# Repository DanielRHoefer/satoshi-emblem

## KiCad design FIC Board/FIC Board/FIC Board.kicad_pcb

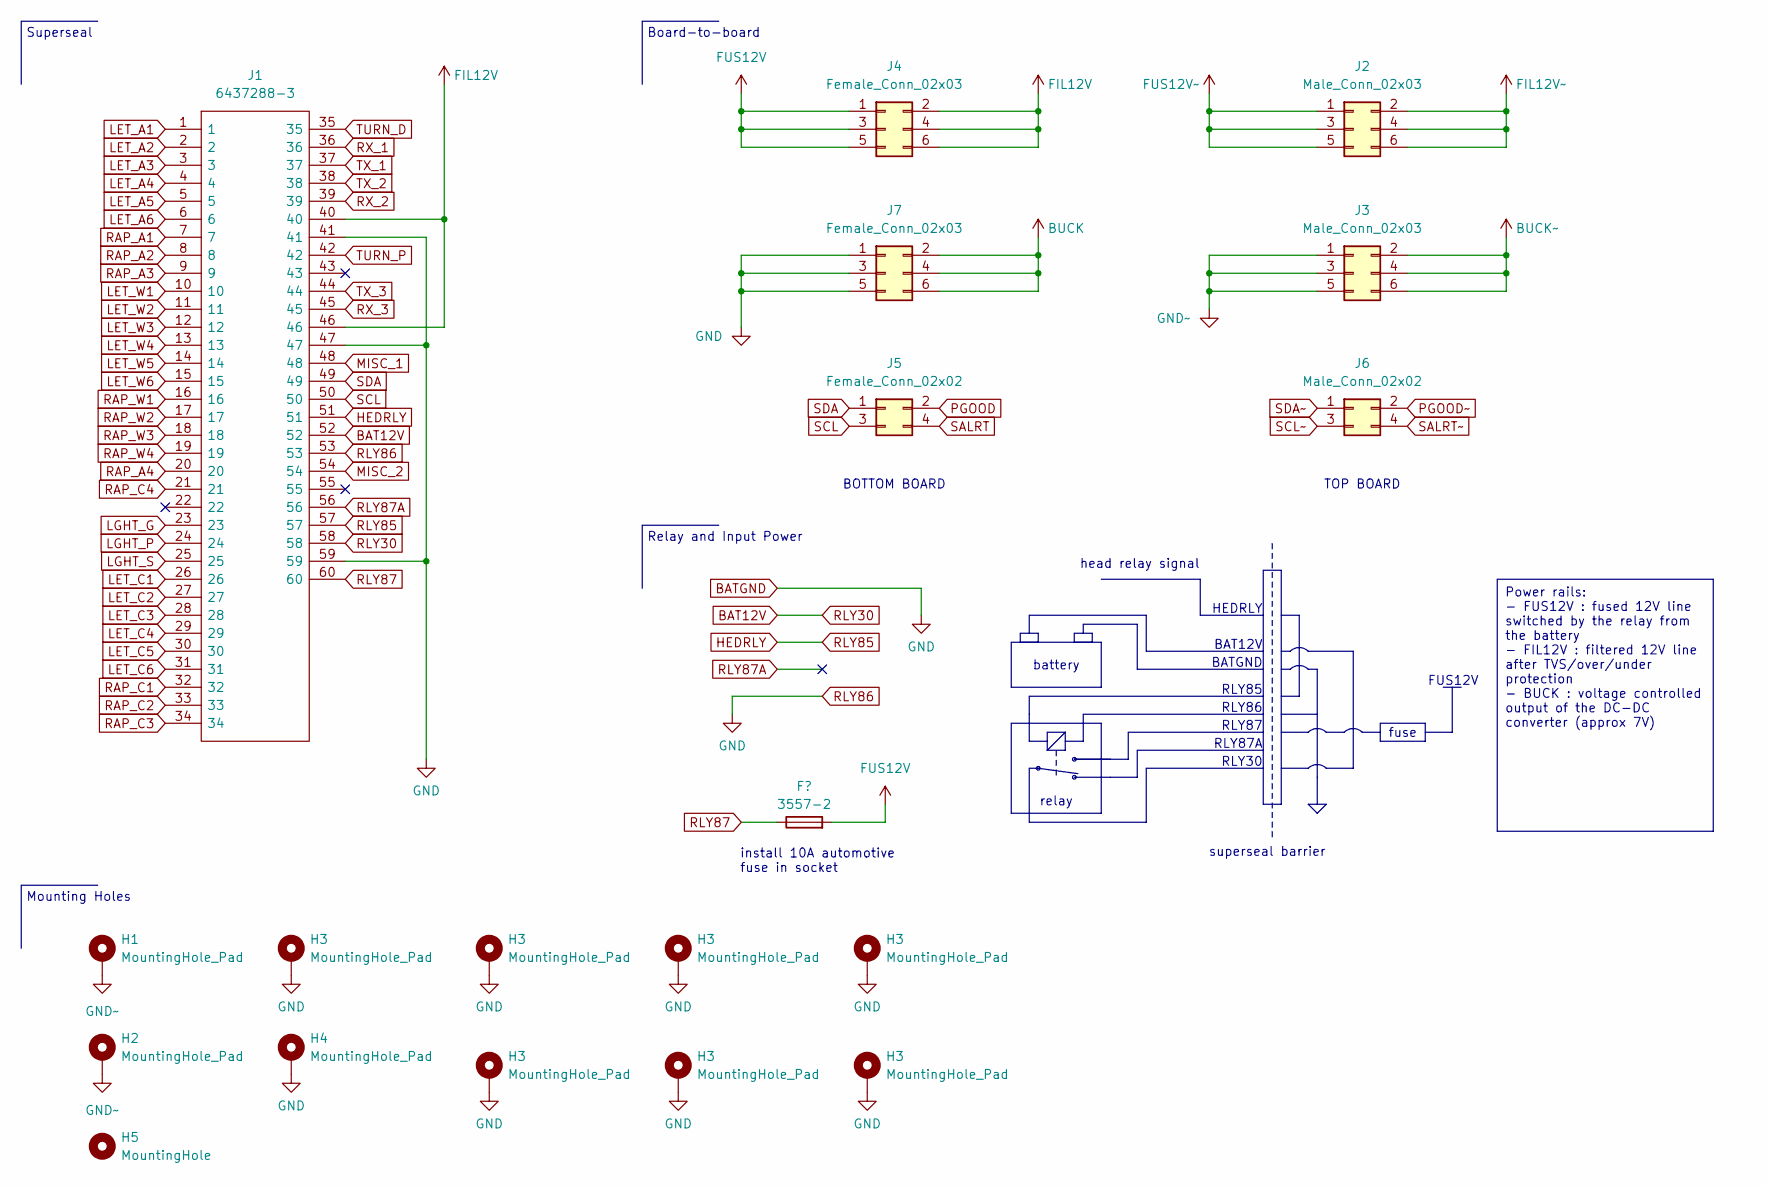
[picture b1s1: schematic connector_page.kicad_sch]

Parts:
F1: 3557-2; Univ_AUTO_Fuse; MPN 3557-2
H1, H2, H3, H4: MountingHole_Pad; MountingHole_2.7mm_M2.5_Pad_TopBottom
H5: MountingHole; MountingHole_2.7mm_M2.5
J1: 6437288-3; 64372885; MPN 6437288-3; Mouser Part Number 571-6437288-5
J2, J3: Conn_02x03_Odd_Even; Male_3x2_Conn
J4: Female_3x2_Conn
J5: Conn_02x02_Odd_Even; Female_2x2_Conn
J6: Conn_02x02_Odd_Even; Male_2x2_Conn
J7: Conn_02x03_Odd_Even; Female_3x2_Conn

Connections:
BAT12V: J1.52, J1.58
BUCK~: J3.2, J3.4, J3.6; also elsewhere on the board
FIL12V: J1.40, J1.46, J4.2, J4.4, J4.6
FIL12V~: J2.2, J2.4, J2.6; also elsewhere on the board
FUS12V: F1.2, J4.1, J4.3, J4.5
FUS12V~: J2.1, J2.3, J2.5; also elsewhere on the board
HEDRLY: J1.51, J1.57
LET_A1: J1.1; also elsewhere on the board
LET_A2: J1.2; also elsewhere on the board
LET_A3: J1.3; also elsewhere on the board
LET_A4: J1.4; also elsewhere on the board
LET_A5: J1.5; also elsewhere on the board
LET_A6: J1.6; also elsewhere on the board
LET_W1: J1.10; also elsewhere on the board
LET_W2: J1.11; also elsewhere on the board
LET_W3: J1.12; also elsewhere on the board
LET_W4: J1.13; also elsewhere on the board
LET_W5: J1.14; also elsewhere on the board
LET_W6: J1.15; also elsewhere on the board
LGHT_S: J1.25; also elsewhere on the board
MISC_1: J1.48; also elsewhere on the board
MISC_2: J1.54; also elsewhere on the board
PGOOD: J5.2; also elsewhere on the board
PGOOD~: J6.2; also elsewhere on the board
RAP_A1: J1.7; also elsewhere on the board
RAP_A2: J1.8; also elsewhere on the board
RAP_A3: J1.9; also elsewhere on the board
RAP_A4: J1.20; also elsewhere on the board
RAP_W1: J1.16; also elsewhere on the board
RAP_W2: J1.17; also elsewhere on the board
RAP_W3: J1.18; also elsewhere on the board
RAP_W4: J1.19; also elsewhere on the board
RLY87: F1.1, J1.60
RLY87A: J1.56
RX_1: J1.36; also elsewhere on the board
RX_2: J1.39; also elsewhere on the board
RX_3: J1.45; also elsewhere on the board
SALRT: J5.4; also elsewhere on the board
SALRT~: J6.4; also elsewhere on the board
SCL~: J6.3; also elsewhere on the board
SDA~: J6.1; also elsewhere on the board
TURN_D: J1.35; also elsewhere on the board
TURN_P: J1.42; also elsewhere on the board
TX_1: J1.37; also elsewhere on the board
TX_2: J1.38; also elsewhere on the board
TX_3: J1.44; also elsewhere on the board

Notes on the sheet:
fuse
relay
battery
install 10A automotive fuse in socket
BOTTOM BOARD
TOP BOARD
Power rails: - FUS12V : fused 12V line switched by the relay from the battery - FIL12V : filtered 12V line after TVS/over/under protection - BUCK : voltage controlled output of the DC-DC converter (approx 7V)
Board-to-board
Mounting Holes
BATGND
RLY87
BAT12V
RLY86
head relay signal
superseal barrier
HEDRLY
FUS12V
RLY30
RLY87A
Superseal
Relay and Input Power
RLY85

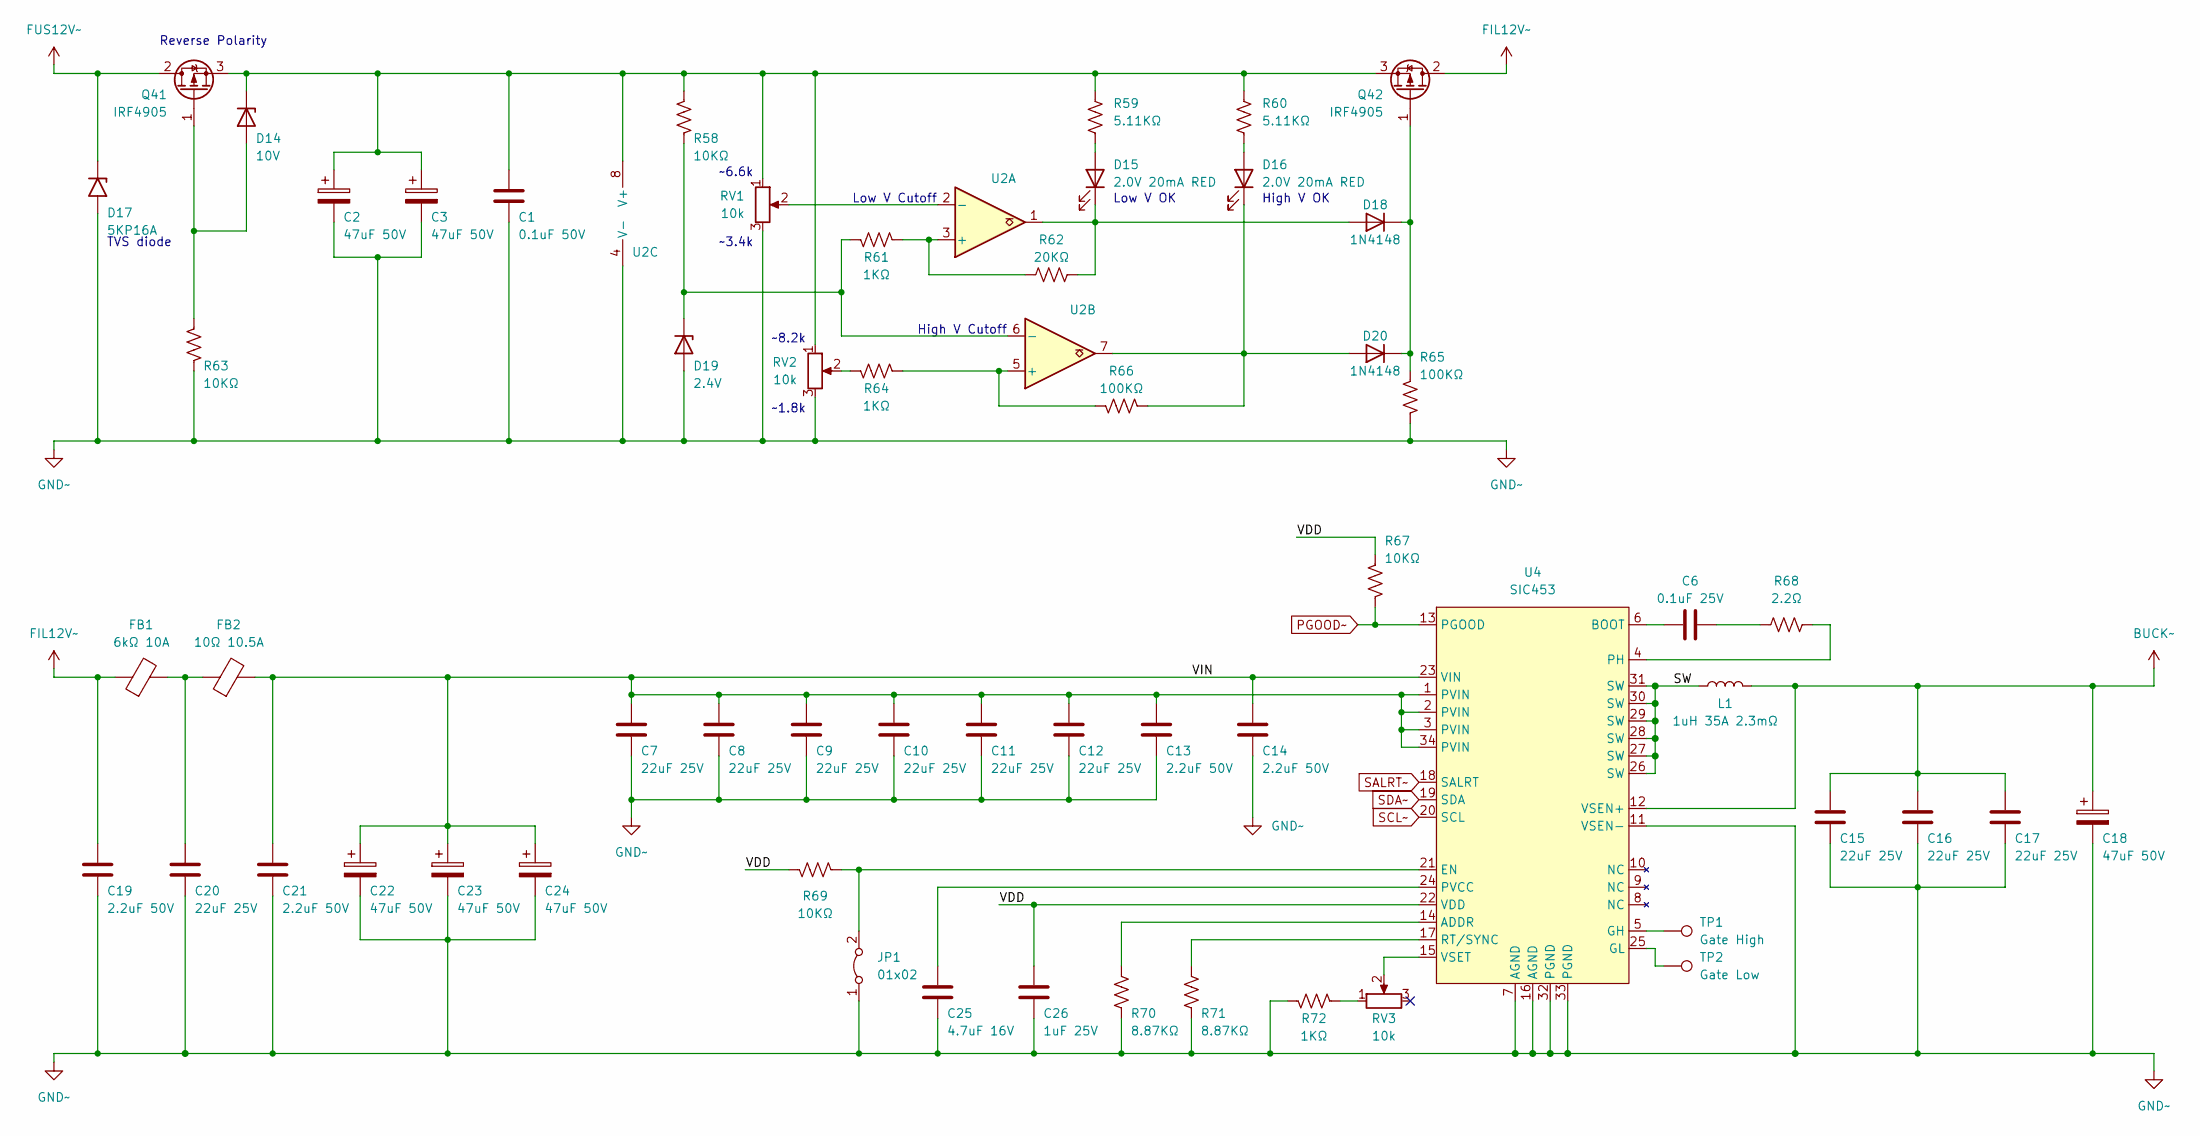
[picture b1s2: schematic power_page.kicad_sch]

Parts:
C1: 0.1u 50V; C_Disc_D4.7mm_W2.5mm_P5.00mm; MPN C322C104K5R5TA7317
C2, C3, C18, C22, C23, C24: 47uF 50V; CP_Elec_6.3x5.9; MPN 865080645012
C6: 0.1uF; C_0603_1608Metric; MPN KGM15BR71E104KM
C7, C8, C9, C10, C11, C12, C15, C16, C17, C20: 22uF 25V; C_1210_3225Metric; MPN CL32B226KAJNNNE
C13, C14, C19, C21: 2.2uF 50V; C_0603_1608Metric; MPN GRM188R61H225ME11D
C25: 4.7u; C_0603_1608Metric; MPN GRM188Z71C475KE21J
C26: 1uF 25V; C_0603_1608Metric; MPN CL10B105KA8NNNC
D14: 10V Zener SOD-80; D_MiniMELF; MPN BZT55B10-GS08
D15, D16: LED_0603_1608Metric; MPN LTST-C191KRKT
D17: 5KP16A; D_P600_R-6_P20.00mm_Horizontal; MPN 5KP16A
D18, D20: 1N4148W-13-F; D_SOD-123; MPN 1N4148W-13-F
D19: 2.4V Zener SOD-80; D_MiniMELF; MPN TZM5221B-GS08
FB1: 74279221100; L_1206_3216Metric_Pad1.22x1.90mm_HandSolder; MPN 742792903
FB2: 74279221100; Wurth 742792903 L_12x12mm_H8mm; MPN 74279221100
JP1: Jumper_2_Bridged; MaleHeader_1x2_conn
L1: SRP1265C-1R0M; INDPM135126X650N; MPN SRP1265C-1R0M
Q41, Q42: IRF4905; TO-263-2; MPN IRF4905STRLPBF
R58, R63, R67, R69: 10KΩ 0603; R_0603_1608Metric; MPN RNCP0603FTD10K0
R59, R60: 5.11KΩ; R_0603_1608Metric; MPN RNCP0603FTD5K11
R61, R64, R72: 1KΩ 0603; R_0603_1608Metric; MPN RNCP0603FTD1K00
R62: 20K; R_0603_1608Metric; MPN RNCP0603FTD20K0
R65, R66: 100KΩ 0603; R_0603_1608Metric; MPN ERJ-H3EF1003V
R68: 2.2Ω; R_0603_1608Metric; MPN RC0603FR-072R2L
R70, R71: 8.87KΩ; R_0603_1608Metric; MPN CRCW06038R87FKEA
RV1, RV2, RV3: 10k; Potentiometer_Bourns_3296X_Horizontal; MPN 3296X-1-103LF
TP1, TP2: TestPoint; TestPoint_Pad_1.0x1.0mm
U2: LM393DR; SOIC-8_3.9x4.9mm_P1.27mm; MPN LM393DR
U4: SIC453ED-T1-GE3; SiC45X; MPN SIC453ED-T1-GE3

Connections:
/POWER/SW: L1.1, U4.26 (SW), U4.27 (SW), U4.28 (SW), U4.29 (SW), U4.30 (SW), U4.31 (SW)
/POWER/VDD: C26.1, R67.1, R69.1, U4.22 (VDD)
/POWER/VIN: C7.1, C8.1, C9.1, C10.1, C11.1, C12.1, C13.1, C14.1, C21.1, C22.1, C23.1, C24.1, FB2.2, U4.1 (PVIN), U4.2 (PVIN), U4.3 (PVIN), U4.23 (VIN), U4.34 (PVIN)
BUCK~: C15.1, C16.1, C17.1, C18.1, L1.2, U4.12 (VSEN+); also elsewhere on the board
FIL12V~: C19.1, FB1.1, Q42.2 (D); also elsewhere on the board
FUS12V~: D17.1 (A1), Q41.2 (D); also elsewhere on the board
unnamed: C20.1, FB1.2, FB2.1
unnamed: D14.2 (A), Q41.1 (G), R63.1
unnamed: D15.2 (A), R59.2
unnamed: D15.1 (K), D18.2 (A), R62.2, U2.1
unnamed: D16.2 (A), R60.2
unnamed: D16.1 (K), D20.2 (A), R66.2, U2.7
unnamed: D18.1 (K), D20.1 (K), Q42.1 (G), R65.1
unnamed: JP1.2 (B), R69.2, U4.21 (EN)
unnamed: R64.1, RV2.2
unnamed: R72.2, RV3.1
unnamed: R61.2, R62.1, U2.3 (+)
unnamed: RV1.2, U2.2 (-)
unnamed: R64.2, R66.1, U2.5 (+)
unnamed: R70.1, U4.14 (ADDR)
unnamed: TP1.1, U4.5 (GH)
unnamed: TP2.1, U4.25 (GL)
unnamed: R68.2, U4.4 (PH)
unnamed: C25.1, U4.24 (PVCC)
unnamed: R71.1, U4.17 (RT/SYNC)
unnamed: RV3.2, U4.15 (VSET)
PGOOD~: R67.2, U4.13 (PGOOD); also elsewhere on the board
SALRT~: U4.18 (SALRT); also elsewhere on the board
SCL~: U4.20 (SCL); also elsewhere on the board
SDA~: U4.19 (SDA); also elsewhere on the board

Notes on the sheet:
~8.2k
~3.4k
Reverse Polarity
High V Cutoff
~6.6k
Low V OK
TVS diode
Low V Cutoff
~1.8k
High V OK

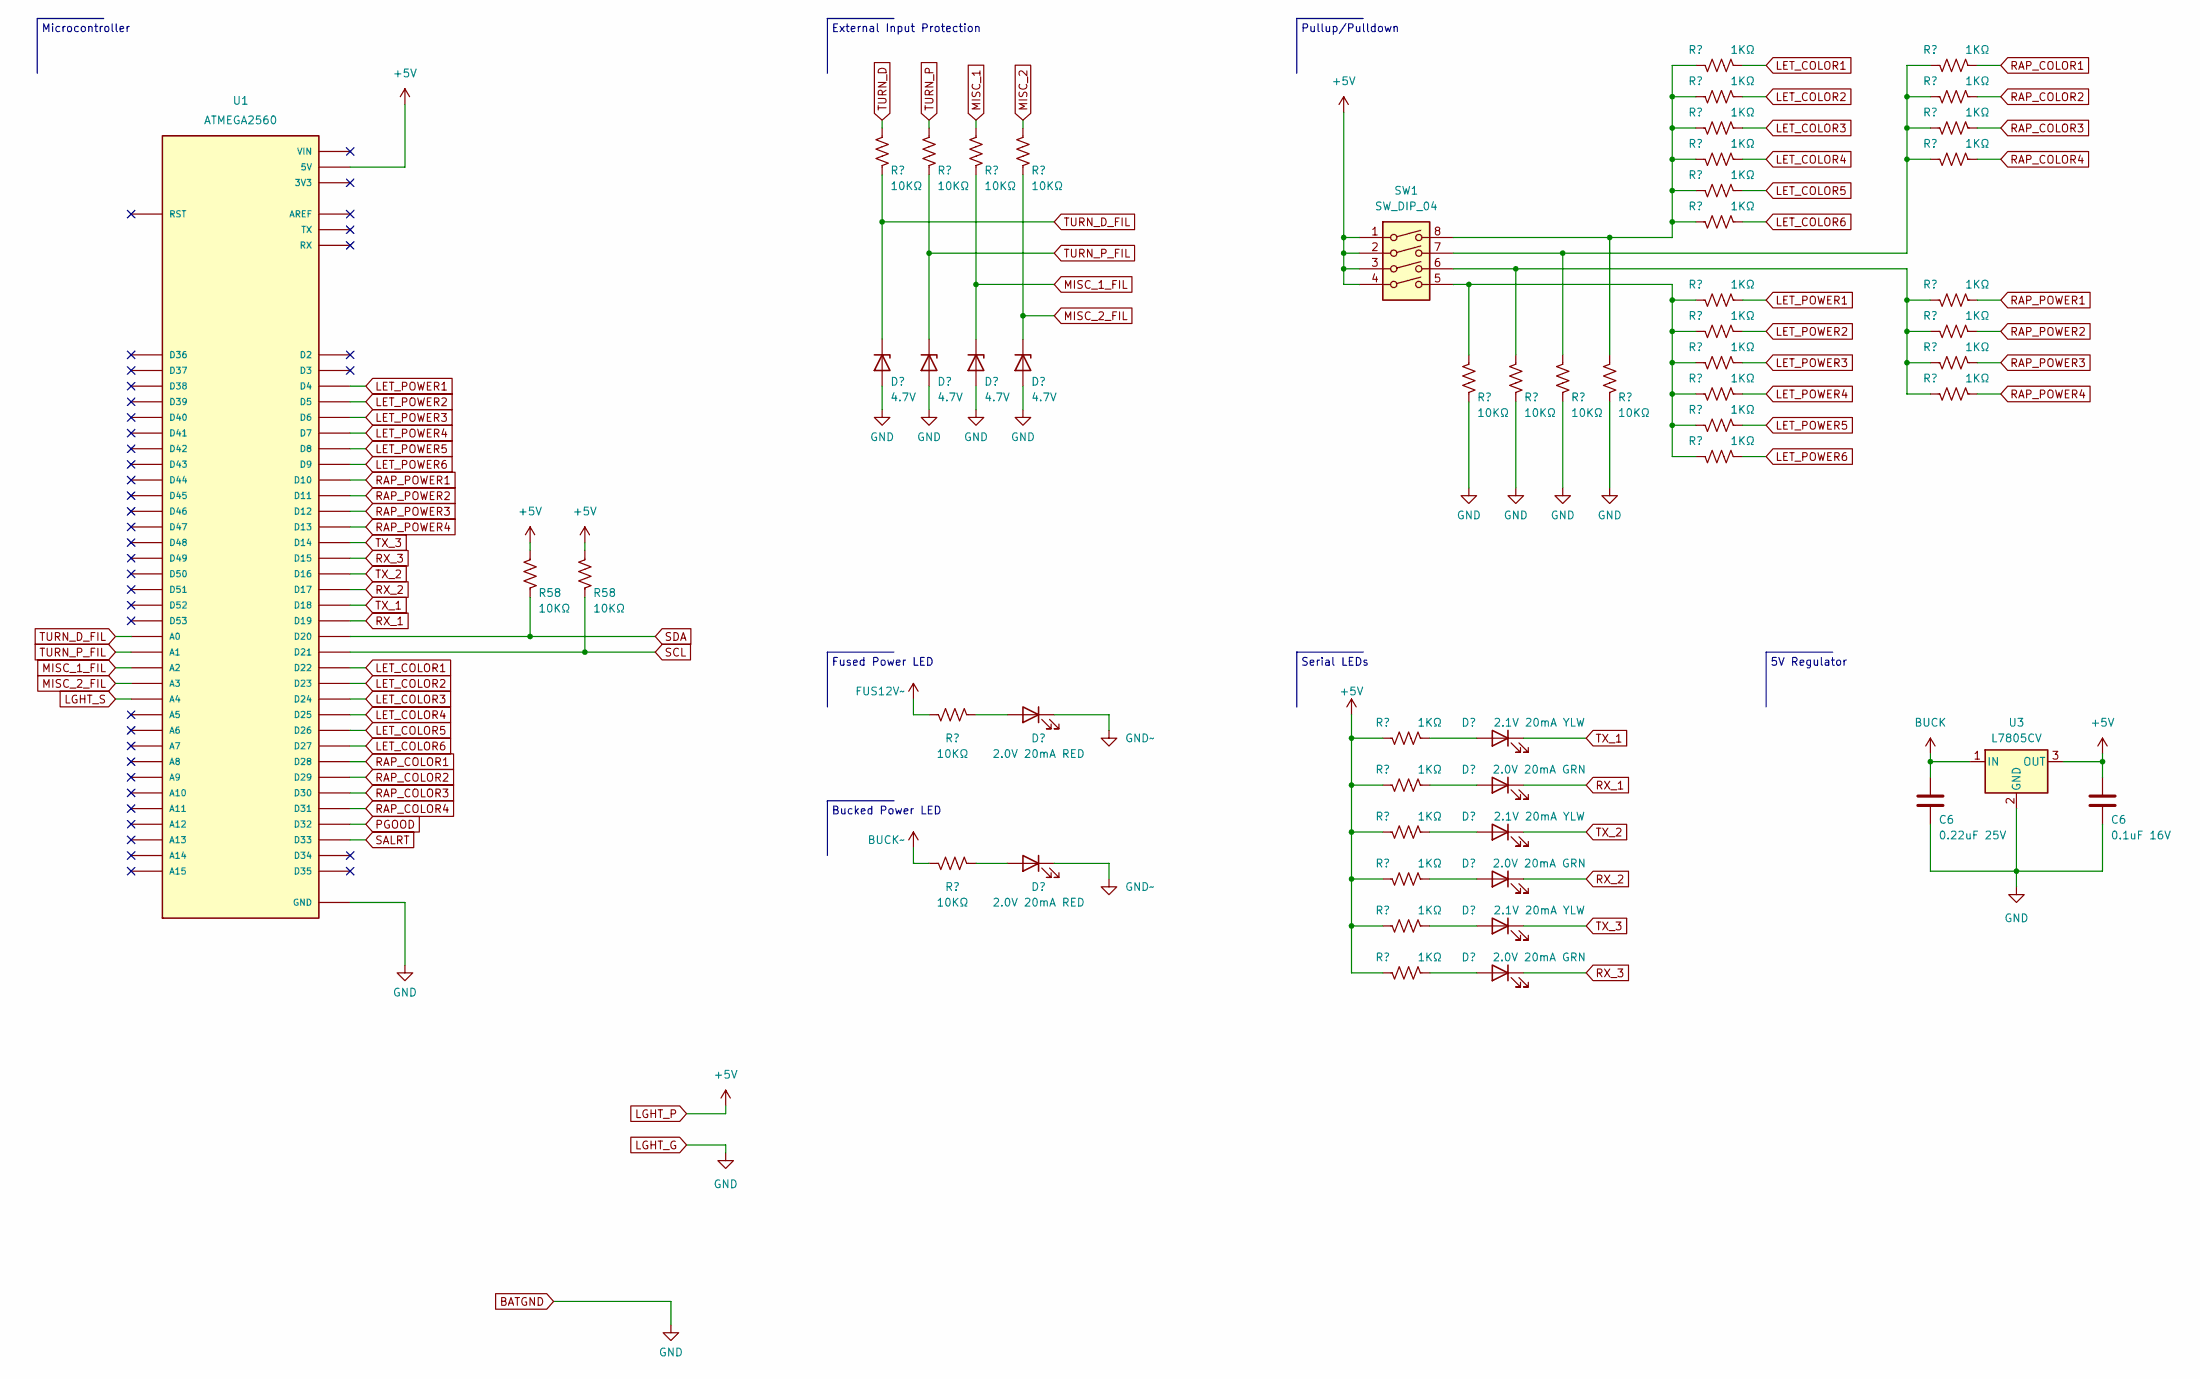
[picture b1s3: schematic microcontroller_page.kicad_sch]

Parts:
C6: KGM15BR51E224KT; C_0603_1608Metric; MPN KGM15BR51E224KT
D1: Diode_SMD:D_MiniMELF; D_MiniMELF; MPN BZT55C4V7-GS08
D2, D3, D4: 4.7V Zener SOD-80; D_MiniMELF; MPN BZT55C4V7-GS08
D6, D8, D11: 2.1V 20mA YLW 0603; LED_0603_1608Metric; MPN LTST-C191KSKT
D7, D10, D12: 2.0V 20mA GRN 0603; LED_0603_1608Metric; MPN LTST-C191KGKT
D9, D13: 2.0V 20mA RED 0603; LED_0603_1608Metric; MPN LTST-C191KRKT
R1, R2, R3, R4, R5, R6, R11, R12, R13, R14, R15, R16, R17, R18, R19, R20, R25, R26, R27, R28, R30, R31, R32, R34, R35, R36: 1KΩ 0603; R_0603_1608Metric; MPN RNCP0603FTD1K00
R7, R8, R9, R10, R21, R22, R23, R24, R33, R37, R58: 10KΩ 0603; R_0603_1608Metric; MPN RNCP0603FTD10K0
SW1: SW_DIP_04; SW_DIP_SPSTx04_Slide_9.78x12.34mm_W7.62mm_P2.54mm; MPN DS01C-254-L-04BE
U1: MEGA_PRO_EMBED_CH340G_/_ATMEGA2560; MODULE_MEGA_PRO_EMBED_CH340G___ATMEGA2560; PARTREV 12/May/2017
U3: L7805CV; TO-220-3_Horizontal_TabDown; MPN L7805CV

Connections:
BUCK~: R37.1; also elsewhere on the board
FUS12V~: R33.1; also elsewhere on the board
LET_COLOR1: R1.2, U1.D22; also elsewhere on the board
LET_COLOR2: R3.2, U1.D23; also elsewhere on the board
LET_COLOR3: R5.2, U1.D24; also elsewhere on the board
LET_COLOR4: R11.2, U1.D25; also elsewhere on the board
LET_COLOR5: R13.2, U1.D26; also elsewhere on the board
LET_COLOR6: R14.2, U1.D27; also elsewhere on the board
LET_POWER1: R15.2, U1.D4; also elsewhere on the board
LET_POWER2: R17.2, U1.D5; also elsewhere on the board
LET_POWER3: R19.2, U1.D6; also elsewhere on the board
LET_POWER4: R25.2, U1.D7; also elsewhere on the board
LET_POWER5: R27.2, U1.D8; also elsewhere on the board
LET_POWER6: R28.2, U1.D9; also elsewhere on the board
LGHT_S: U1.A4; also elsewhere on the board
MISC_1: R9.1; also elsewhere on the board
MISC_1_FIL: D3.1 (K), R9.2, U1.A2
MISC_2: R10.1; also elsewhere on the board
MISC_2_FIL: D4.1 (K), R10.2, U1.A3
unnamed: D6.2 (A), R30.2
unnamed: D7.2 (A), R31.2
unnamed: D8.2 (A), R32.2
unnamed: D9.2 (A), R33.2
unnamed: D10.2 (A), R34.2
unnamed: D11.2 (A), R35.2
unnamed: D12.2 (A), R36.2
unnamed: D13.2 (A), R37.2
unnamed: R1.1, R3.1, R5.1, R11.1, R13.1, R14.1, R24.1, SW1.8
unnamed: R2.1, R4.1, R6.1, R12.1, R23.1, SW1.7
unnamed: R15.1, R17.1, R19.1, R21.1, R25.1, R27.1, R28.1, SW1.5
unnamed: R16.1, R18.1, R20.1, R22.1, R26.1, SW1.6
PGOOD: U1.D32; also elsewhere on the board
RAP_COLOR1: R2.2, U1.D28; also elsewhere on the board
RAP_COLOR2: R4.2, U1.D29; also elsewhere on the board
RAP_COLOR3: R6.2, U1.D30; also elsewhere on the board
RAP_POWER1: R16.2, U1.D10; also elsewhere on the board
RAP_POWER2: R18.2, U1.D11; also elsewhere on the board
RAP_POWER3: R20.2, U1.D12; also elsewhere on the board
RAP_POWER4: R26.2, U1.D13; also elsewhere on the board
RX_1: D7.1 (K), U1.D19; also elsewhere on the board
RX_2: D10.1 (K), U1.D17; also elsewhere on the board
RX_3: D12.1 (K), U1.D15; also elsewhere on the board
SALRT: U1.D33; also elsewhere on the board
TURN_D: R7.1; also elsewhere on the board
TURN_D_FIL: D1.1 (K), R7.2, U1.A0
TURN_P: R8.1; also elsewhere on the board
TURN_P_FIL: D2.1 (K), R8.2, U1.A1
TX_1: D6.1 (K), U1.D18; also elsewhere on the board
TX_2: D8.1 (K), U1.D16; also elsewhere on the board
TX_3: D11.1 (K), U1.D14; also elsewhere on the board

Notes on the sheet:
Fused Power LED
Bucked Power LED
Pullup/Pulldown
Serial LEDs
5V Regulator
Microcontroller
External Input Protection

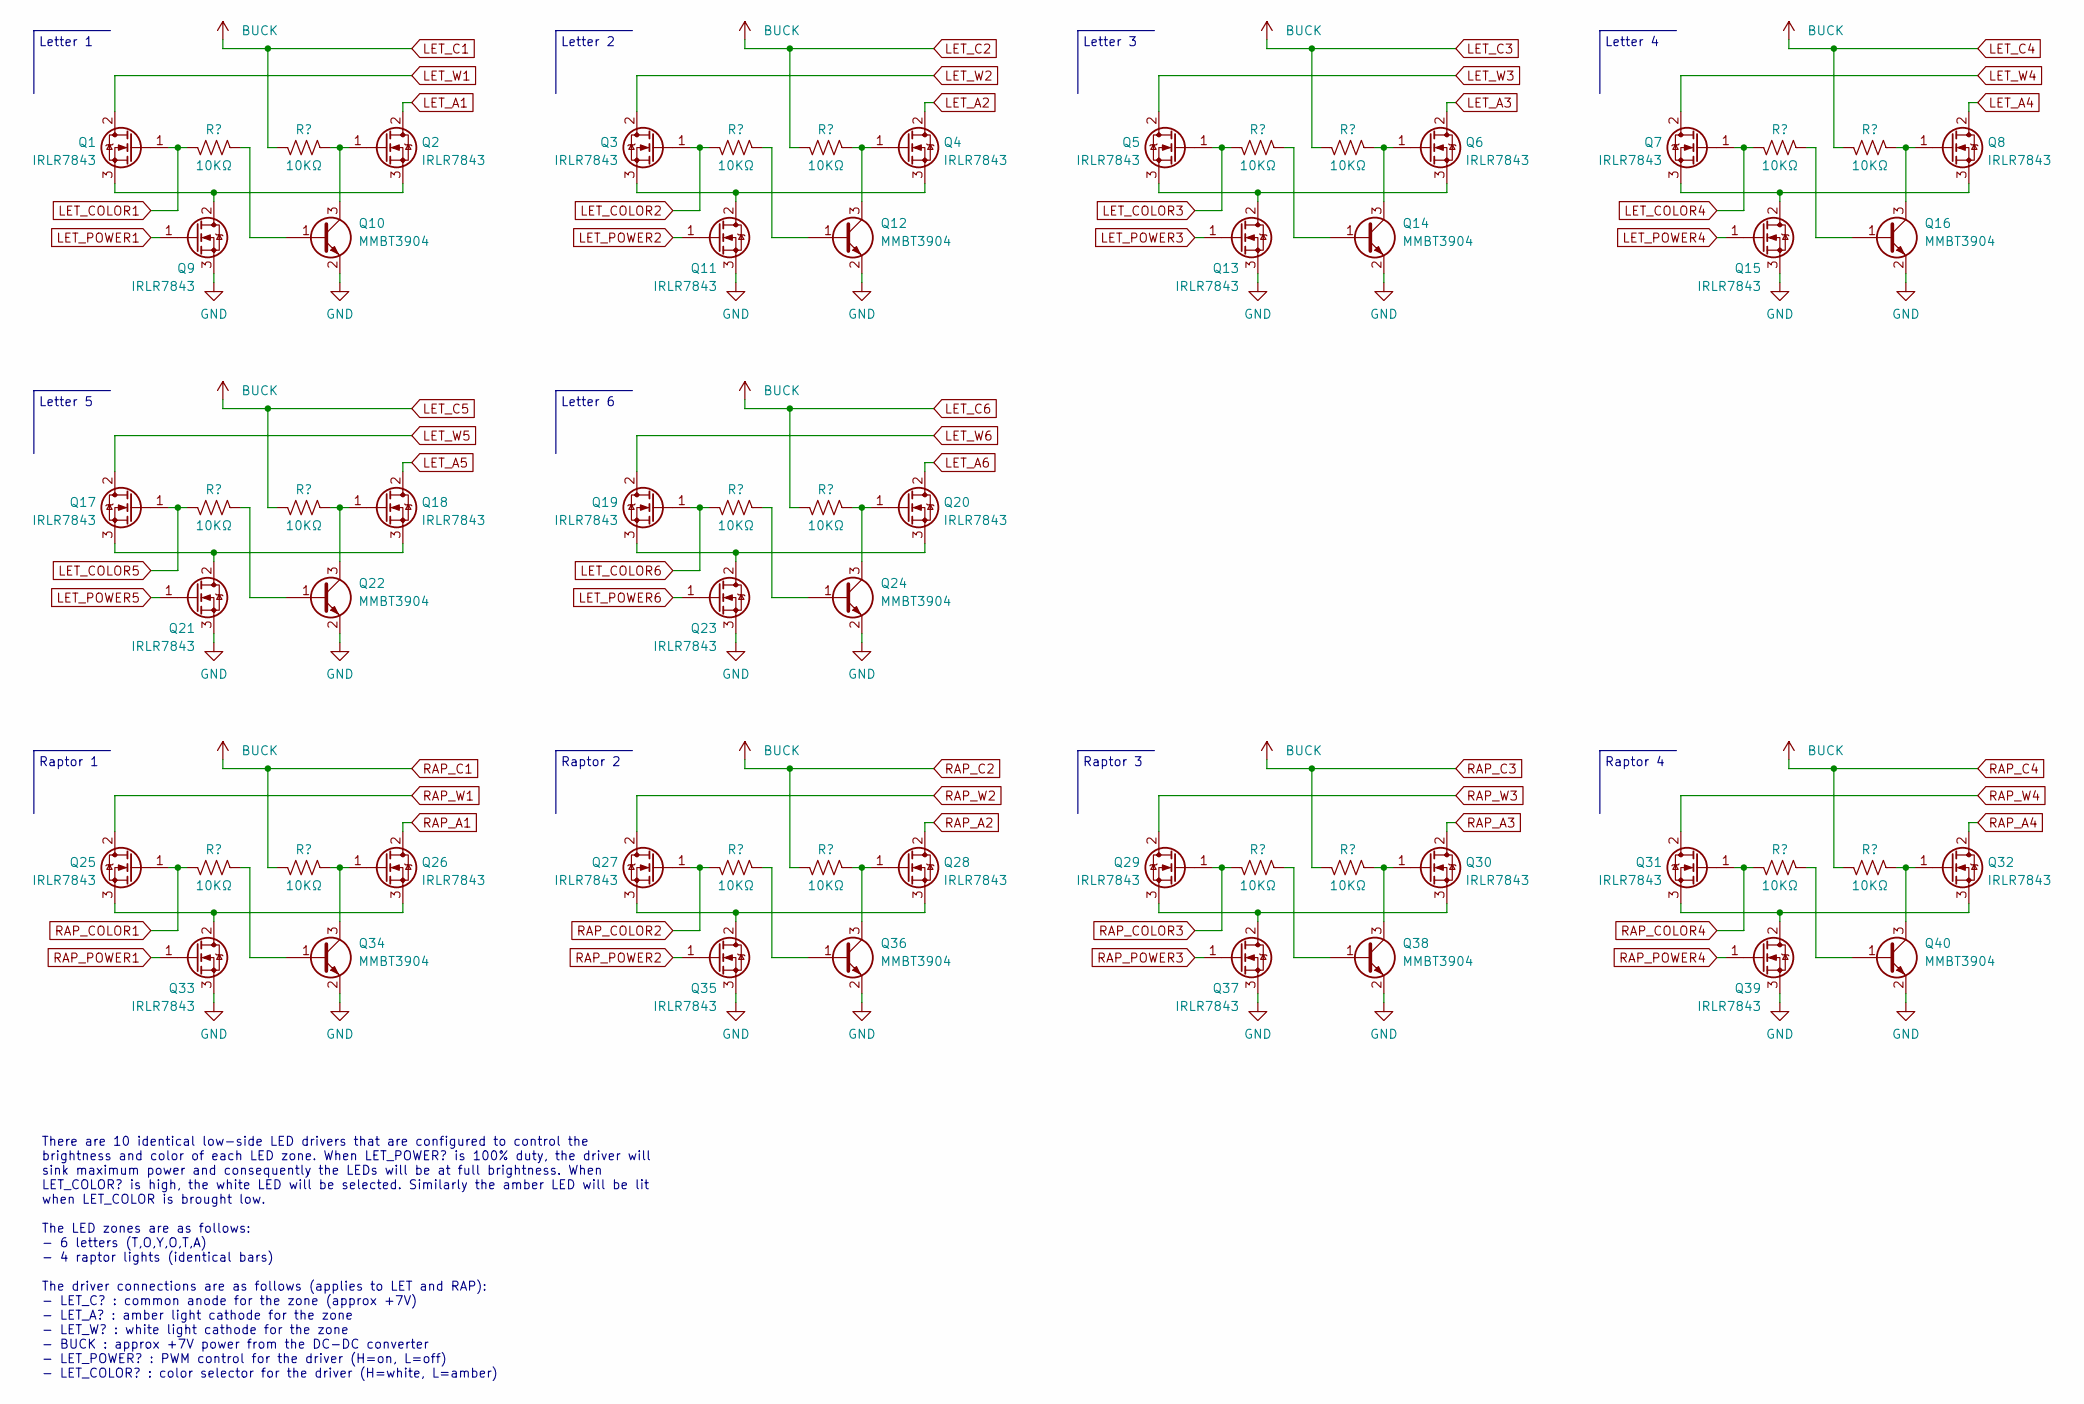
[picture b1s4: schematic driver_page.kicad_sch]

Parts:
Q1, Q2, Q3, Q4, Q5, Q6, Q7, Q8, Q9, Q11, Q13, Q15, Q17, Q18, Q19, Q20, Q21, Q23, Q25, Q26, Q27, Q28, Q29, Q30, Q31, Q32, Q33, Q35, Q37, Q39: IRLR7843; TO-252-2; MPN IRLR7843TRPBF
Q10, Q12, Q14, Q16, Q22, Q24, Q34, Q36, Q38, Q40: MMBT3904; SOT-23; MPN MMBT3904
R38, R39, R40, R41, R42, R43, R44, R45, R46, R47, R48, R49, R50, R51, R52, R53, R54, R55, R56, R57: 10KΩ 0603; R_0603_1608Metric; MPN RNCP0603FTD10K0

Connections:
LET_A1: Q2.2 (D); also elsewhere on the board
LET_A2: Q4.2 (D); also elsewhere on the board
LET_A3: Q6.2 (D); also elsewhere on the board
LET_A4: Q8.2 (D); also elsewhere on the board
LET_A5: Q18.2 (D); also elsewhere on the board
LET_A6: Q20.2 (D); also elsewhere on the board
LET_COLOR1: Q1.1 (G), R38.1; also elsewhere on the board
LET_COLOR2: Q3.1 (G), R40.1; also elsewhere on the board
LET_COLOR3: Q5.1 (G), R42.1; also elsewhere on the board
LET_COLOR4: Q7.1 (G), R44.1; also elsewhere on the board
LET_COLOR5: Q17.1 (G), R46.1; also elsewhere on the board
LET_COLOR6: Q19.1 (G), R48.1; also elsewhere on the board
LET_POWER1: Q9.1 (G); also elsewhere on the board
LET_POWER2: Q11.1 (G); also elsewhere on the board
LET_POWER3: Q13.1 (G); also elsewhere on the board
LET_POWER4: Q15.1 (G); also elsewhere on the board
LET_POWER5: Q21.1 (G); also elsewhere on the board
LET_POWER6: Q23.1 (G); also elsewhere on the board
LET_W1: Q1.2 (D); also elsewhere on the board
LET_W2: Q3.2 (D); also elsewhere on the board
LET_W3: Q5.2 (D); also elsewhere on the board
LET_W4: Q7.2 (D); also elsewhere on the board
LET_W5: Q17.2 (D); also elsewhere on the board
LET_W6: Q19.2 (D); also elsewhere on the board
unnamed: Q1.3 (S), Q2.3 (S), Q9.2 (D)
unnamed: Q10.1 (B), R38.2
unnamed: Q2.1 (G), Q10.3 (C), R39.2
unnamed: Q3.3 (S), Q4.3 (S), Q11.2 (D)
unnamed: Q12.1 (B), R40.2
unnamed: Q4.1 (G), Q12.3 (C), R41.2
unnamed: Q5.3 (S), Q6.3 (S), Q13.2 (D)
unnamed: Q14.1 (B), R42.2
unnamed: Q6.1 (G), Q14.3 (C), R43.2
unnamed: Q7.3 (S), Q8.3 (S), Q15.2 (D)
unnamed: Q16.1 (B), R44.2
unnamed: Q8.1 (G), Q16.3 (C), R45.2
unnamed: Q17.3 (S), Q18.3 (S), Q21.2 (D)
unnamed: Q18.1 (G), Q22.3 (C), R47.2
unnamed: Q19.3 (S), Q20.3 (S), Q23.2 (D)
unnamed: Q20.1 (G), Q24.3 (C), R49.2
unnamed: Q22.1 (B), R46.2
unnamed: Q24.1 (B), R48.2
unnamed: Q25.3 (S), Q26.3 (S), Q33.2 (D)
unnamed: Q26.1 (G), Q34.3 (C), R51.2
unnamed: Q27.3 (S), Q28.3 (S), Q35.2 (D)
unnamed: Q28.1 (G), Q36.3 (C), R53.2
unnamed: Q29.3 (S), Q30.3 (S), Q37.2 (D)
unnamed: Q30.1 (G), Q38.3 (C), R55.2
unnamed: Q31.3 (S), Q32.3 (S), Q39.2 (D)
unnamed: Q32.1 (G), Q40.3 (C), R57.2
unnamed: Q34.1 (B), R50.2
unnamed: Q36.1 (B), R52.2
unnamed: Q38.1 (B), R54.2
RAP_A1: Q26.2 (D); also elsewhere on the board
RAP_A2: Q28.2 (D); also elsewhere on the board
RAP_A3: Q30.2 (D); also elsewhere on the board
RAP_A4: Q32.2 (D); also elsewhere on the board
RAP_COLOR1: Q25.1 (G), R50.1; also elsewhere on the board
RAP_COLOR2: Q27.1 (G), R52.1; also elsewhere on the board
RAP_COLOR3: Q29.1 (G), R54.1; also elsewhere on the board
RAP_POWER1: Q33.1 (G); also elsewhere on the board
RAP_POWER2: Q35.1 (G); also elsewhere on the board
RAP_POWER3: Q37.1 (G); also elsewhere on the board
RAP_POWER4: Q39.1 (G); also elsewhere on the board
RAP_W1: Q25.2 (D); also elsewhere on the board
RAP_W2: Q27.2 (D); also elsewhere on the board
RAP_W3: Q29.2 (D); also elsewhere on the board
RAP_W4: Q31.2 (D); also elsewhere on the board

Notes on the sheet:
There are 10 identical low-side LED drivers that are configured to control the brightness and color of each LED zone. When LET_POWER? is 100% duty, the driver will sink maximum power and consequently the LEDs will be at full brightness. When LET_COLOR? is high, the white LED will be selected. Simil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
Letter 3
Raptor 2
Letter 4
Raptor 4
Letter 5
Letter 6
Letter 1
Raptor 1
Letter 2
Raptor 3

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
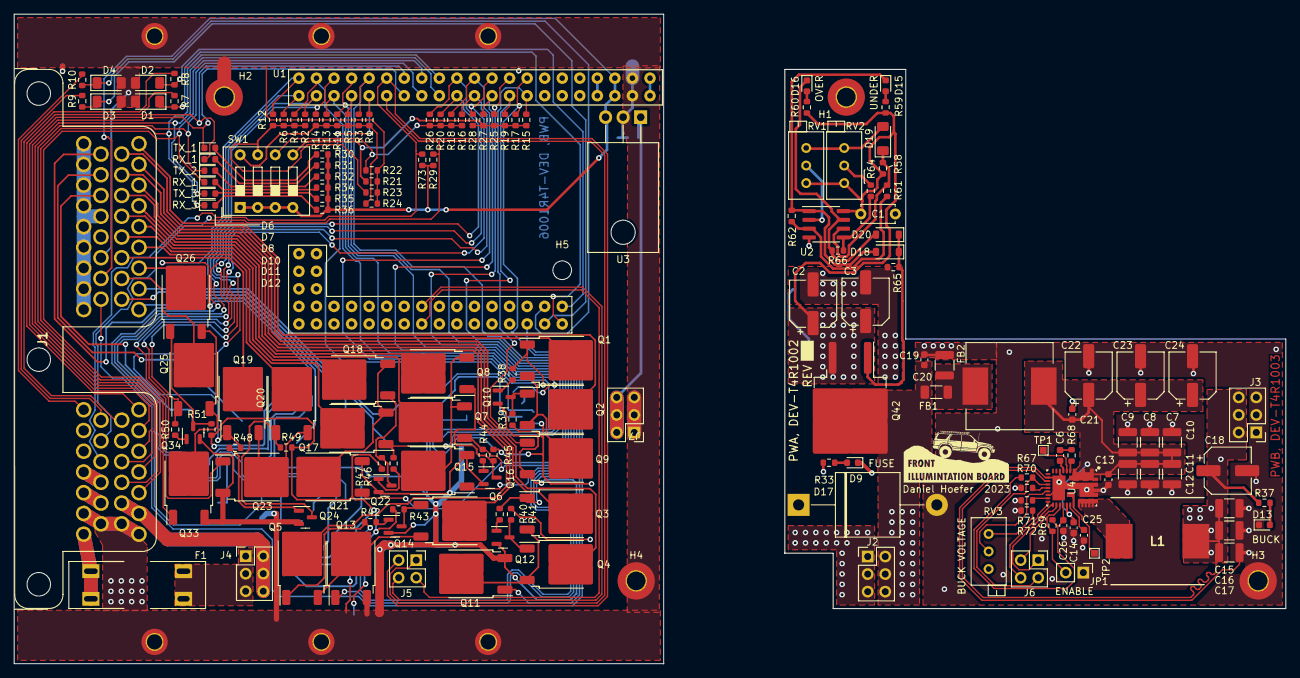
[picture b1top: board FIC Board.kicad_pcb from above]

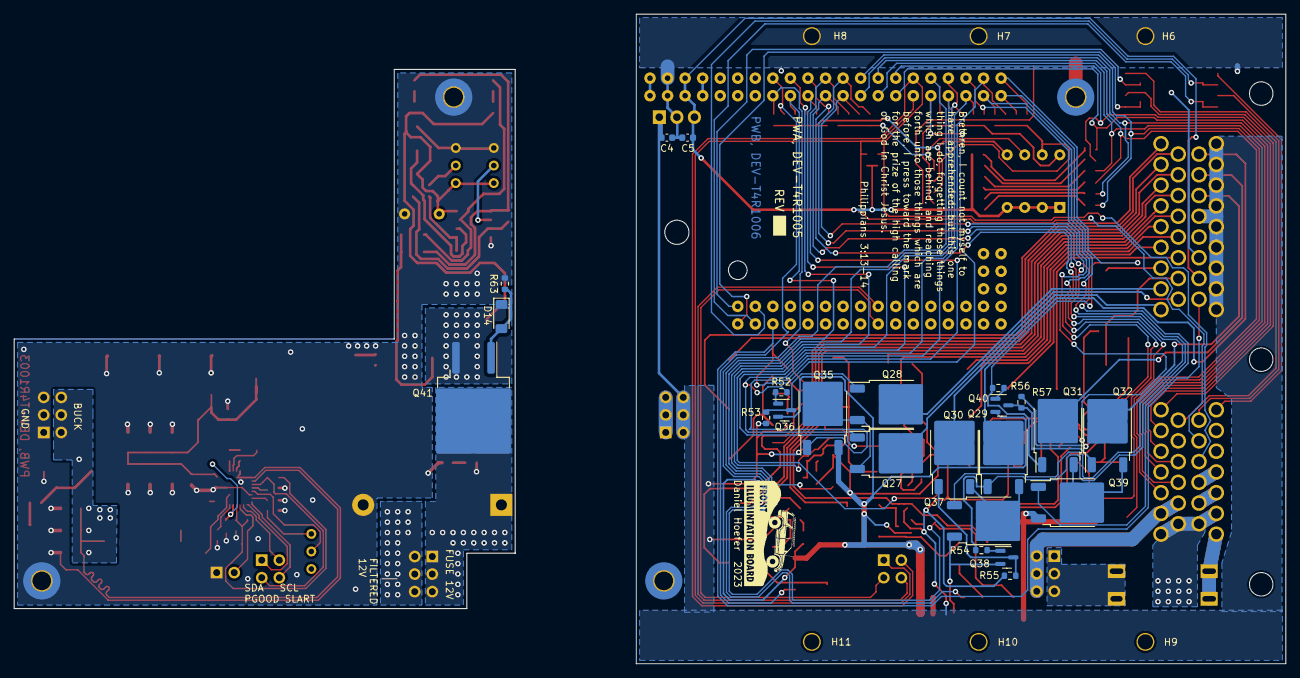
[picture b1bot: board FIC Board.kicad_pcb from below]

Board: 2 copper layers, 184.0 x 94.0 mm, 193 parts (23 on the bottom side), 144 nets.

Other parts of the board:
C4: KGM15BR51E224KT; C_0603_1608Metric
C5: CL10B104KO8NNNC; C_0603_1608Metric
H6, H7, H8, H9, H10, H11: MountingHole_Pad; MountingHole_2.2mm_M2_DIN965_Pad_TopOnly
R29, R73: 10KΩ 0603; R_0603_1608Metric
